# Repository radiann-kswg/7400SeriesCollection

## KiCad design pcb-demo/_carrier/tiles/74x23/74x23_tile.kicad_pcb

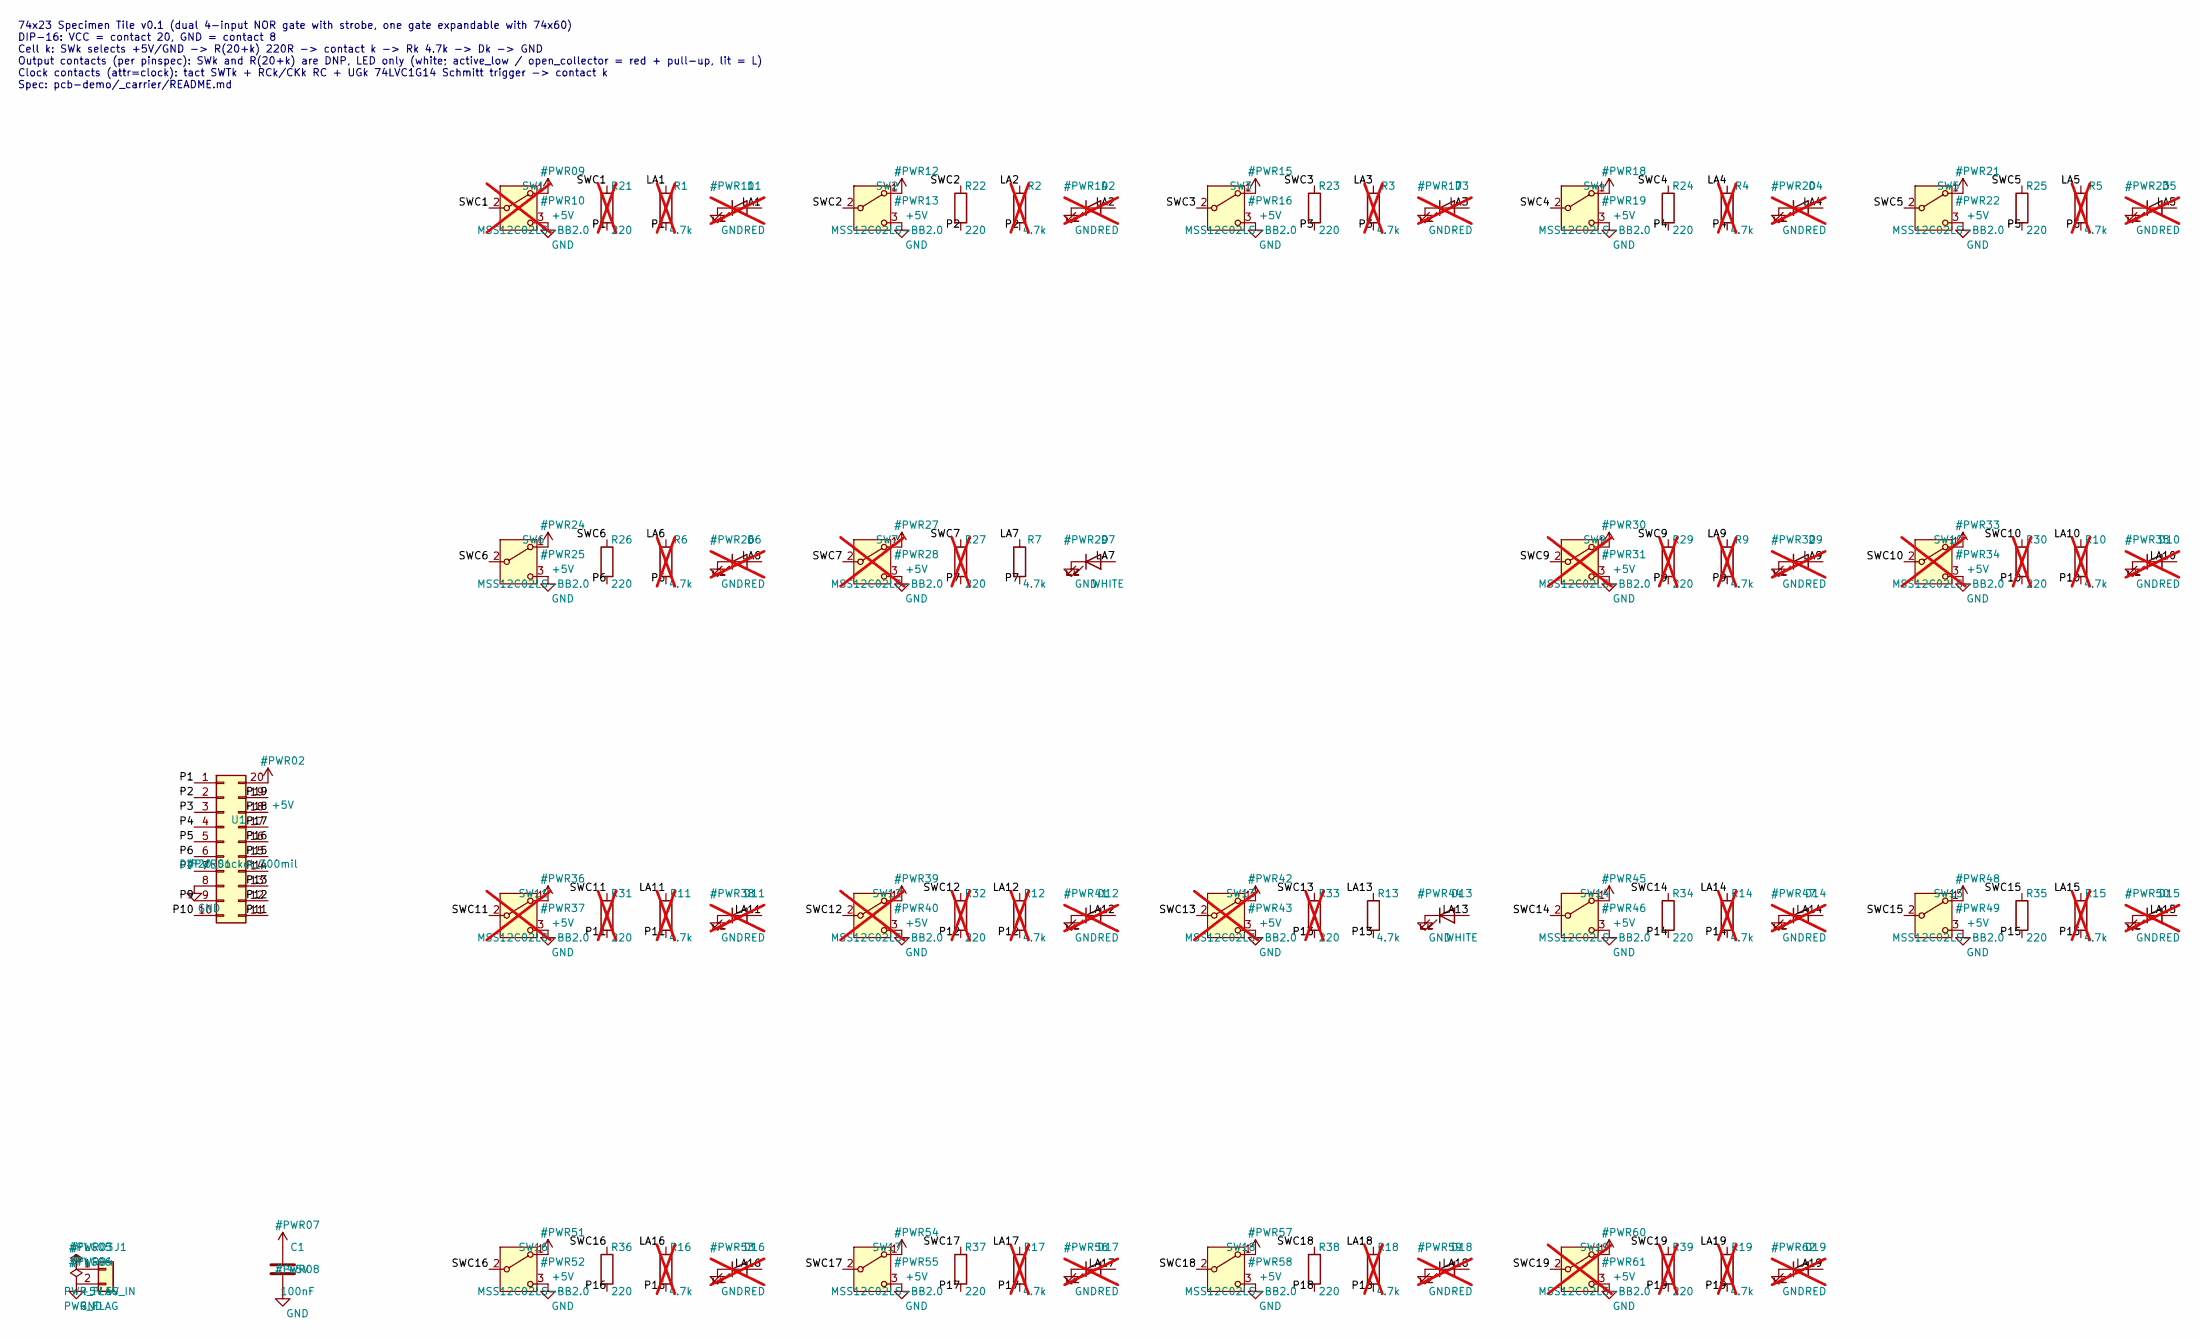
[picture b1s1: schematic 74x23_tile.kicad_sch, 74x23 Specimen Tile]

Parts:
C1: 100nF; C_0603_1608Metric; MPN CC0603KRX7R9BB104; LCSC Part # C14663
D1, D2, D3, D4, D5, D6, D9, D10, D11, D12, D14, D15, D16, D17, D18, D19: RED; LED_0603_1608Metric; MPN KT-0603R; LCSC Part # C2286; not fitted
D7, D13: WHITE; LED_0603_1608Metric; MPN KT-0603W; LCSC Part # C2290
J1: 5V_IN; PinHeader_1x02_P2.54mm_Vertical
R1, R2, R3, R4, R5, R6, R9, R10, R11, R12, R14, R15, R16, R17, R18, R19: 4.7k; R_0603_1608Metric; MPN 0603WAF4701T5E; LCSC Part # C23162; not fitted
R7, R13: 4.7k; R_0603_1608Metric; MPN 0603WAF4701T5E; LCSC Part # C23162
R21, R27, R29, R30, R31, R32, R33, R39: 220; R_0603_1608Metric; MPN 0603WAF2200T5E; LCSC Part # C22962; not fitted
R22, R23, R24, R25, R26, R34, R35, R36, R37, R38: 220; R_0603_1608Metric; MPN 0603WAF2200T5E; LCSC Part # C22962
SW1, SW7, SW9, SW10, SW11, SW12, SW13, SW19: MSS12C02LS-BB2.0; SW_SPDT_Shouhan_MSS12C02LS; MPN MSS12C02LS-BB2.0; LCSC Part # C3008585; not fitted
SW2, SW3, SW4, SW5, SW6, SW14, SW15, SW16, SW17, SW18: MSS12C02LS-BB2.0; SW_SPDT_Shouhan_MSS12C02LS; MPN MSS12C02LS-BB2.0; LCSC Part # C3008585
U1: DIP20_Socket_300mil; DIP-20_W7.62mm_Socket

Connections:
+5V: C1.1, J1.1, SW1.1 (A), SW2.1 (A), SW3.1 (A), SW4.1 (A), SW5.1 (A), SW6.1 (A), SW7.1 (A), SW9.1 (A), SW10.1 (A), SW11.1 (A), SW12.1 (A), SW13.1 (A), SW14.1 (A), SW15.1 (A), SW16.1 (A), SW17.1 (A), SW18.1 (A), SW19.1 (A), U1.20
/LA1: D1.2 (A), R1.1
/LA2: D2.2 (A), R2.1
/LA3: D3.2 (A), R3.1
/LA4: D4.2 (A), R4.1
/LA5: D5.2 (A), R5.1
/LA6: D6.2 (A), R6.1
/LA7: D7.2 (A), R7.1
/LA9: D9.2 (A), R9.1
/LA10: D10.2 (A), R10.1
/LA11: D11.2 (A), R11.1
/LA12: D12.2 (A), R12.1
/LA13: D13.2 (A), R13.1
/LA14: D14.2 (A), R14.1
/LA15: D15.2 (A), R15.1
/LA16: D16.2 (A), R16.1
/LA17: D17.2 (A), R17.1
/LA18: D18.2 (A), R18.1
/LA19: D19.2 (A), R19.1
/P1: R1.2, R21.2, U1.1
/P2: R2.2, R22.2, U1.2
/P3: R3.2, R23.2, U1.3
/P4: R4.2, R24.2, U1.4
/P5: R5.2, R25.2, U1.5
/P6: R6.2, R26.2, U1.6
/P7: R7.2, R27.2, U1.7
/P9: R9.2, R29.2, U1.9
/P10: R10.2, R30.2, U1.10
/P11: R11.2, R31.2, U1.11
/P12: R12.2, R32.2, U1.12
/P13: R13.2, R33.2, U1.13
/P14: R14.2, R34.2, U1.14
/P15: R15.2, R35.2, U1.15
/P16: R16.2, R36.2, U1.16
/P17: R17.2, R37.2, U1.17
/P18: R18.2, R38.2, U1.18
/P19: R19.2, R39.2, U1.19
/SWC1: R21.1, SW1.2 (B)
/SWC2: R22.1, SW2.2 (B)
/SWC3: R23.1, SW3.2 (B)
/SWC4: R24.1, SW4.2 (B)
/SWC5: R25.1, SW5.2 (B)
/SWC6: R26.1, SW6.2 (B)
/SWC7: R27.1, SW7.2 (B)
/SWC9: R29.1, SW9.2 (B)
/SWC10: R30.1, SW10.2 (B)
/SWC11: R31.1, SW11.2 (B)
/SWC12: R32.1, SW12.2 (B)
/SWC13: R33.1, SW13.2 (B)
/SWC14: R34.1, SW14.2 (B)
/SWC15: R35.1, SW15.2 (B)
/SWC16: R36.1, SW16.2 (B)
/SWC17: R37.1, SW17.2 (B)
/SWC18: R38.1, SW18.2 (B)
/SWC19: R39.1, SW19.2 (B)
GND: C1.2, D1.1 (K), D2.1 (K), D3.1 (K), D4.1 (K), D5.1 (K), D6.1 (K), D7.1 (K), D9.1 (K), D10.1 (K), D11.1 (K), D12.1 (K), D13.1 (K), D14.1 (K), D15.1 (K), D16.1 (K), D17.1 (K), D18.1 (K), D19.1 (K), J1.2, SW1.3 (C), SW2.3 (C), SW3.3 (C), SW4.3 (C), SW5.3 (C), SW6.3 (C), SW7.3 (C), SW9.3 (C), SW10.3 (C), SW11.3 (C), SW12.3 (C), SW13.3 (C), SW14.3 (C), SW15.3 (C), SW16.3 (C), SW17.3 (C), SW18.3 (C), SW19.3 (C), U1.8

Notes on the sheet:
74x23 Specimen Tile v0.1 (dual 4-input NOR gate with strobe, one gate expandable with 74x60) DIP-16: VCC = contact 20, GND = contact 8 Cell k: SWk selects +5V/GND -> R(20+k) 220R -> contact k -> Rk 4.7k -> Dk -> GND Output contacts (per pinspec): SWk and R(20+k) are DNP, LED only (white; active_low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

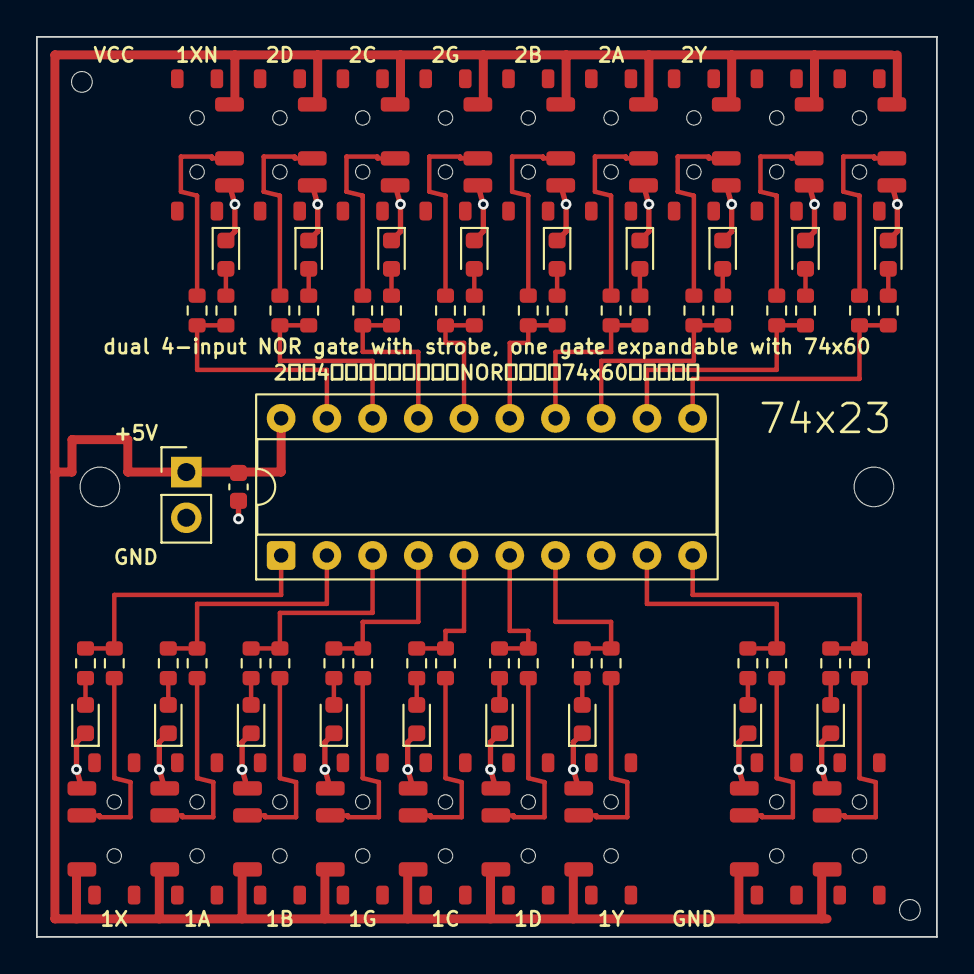
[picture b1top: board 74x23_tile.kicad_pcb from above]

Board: 2 copper layers, 50.0 x 50.0 mm, 79 parts (0 on the bottom side), 56 nets.

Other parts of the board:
MTG1, MTG2: MountingHole_2.2mm_M2
TH1, TH2: ToolingHole_1.152mm

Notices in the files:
pcb-demo/_carrier/tiles/74x23/74x23_tile.kicad_pcb:
MIT License
